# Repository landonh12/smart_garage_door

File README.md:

# Smart Garage Door Controller

This is a PCB made to house a NodeMCU-ESP32S to control my Genie Garage Door. It replaces the wall controller that was installed when we purchased the home.

The original circuit was simple - short RED and WHITE wires to open and close the door, and divide the voltage between RED and WHITE to toggle the garage light.

I used FETs for this - RFP30N06LEs to be exact. The board also supports STD26P3LLH6 FETs.

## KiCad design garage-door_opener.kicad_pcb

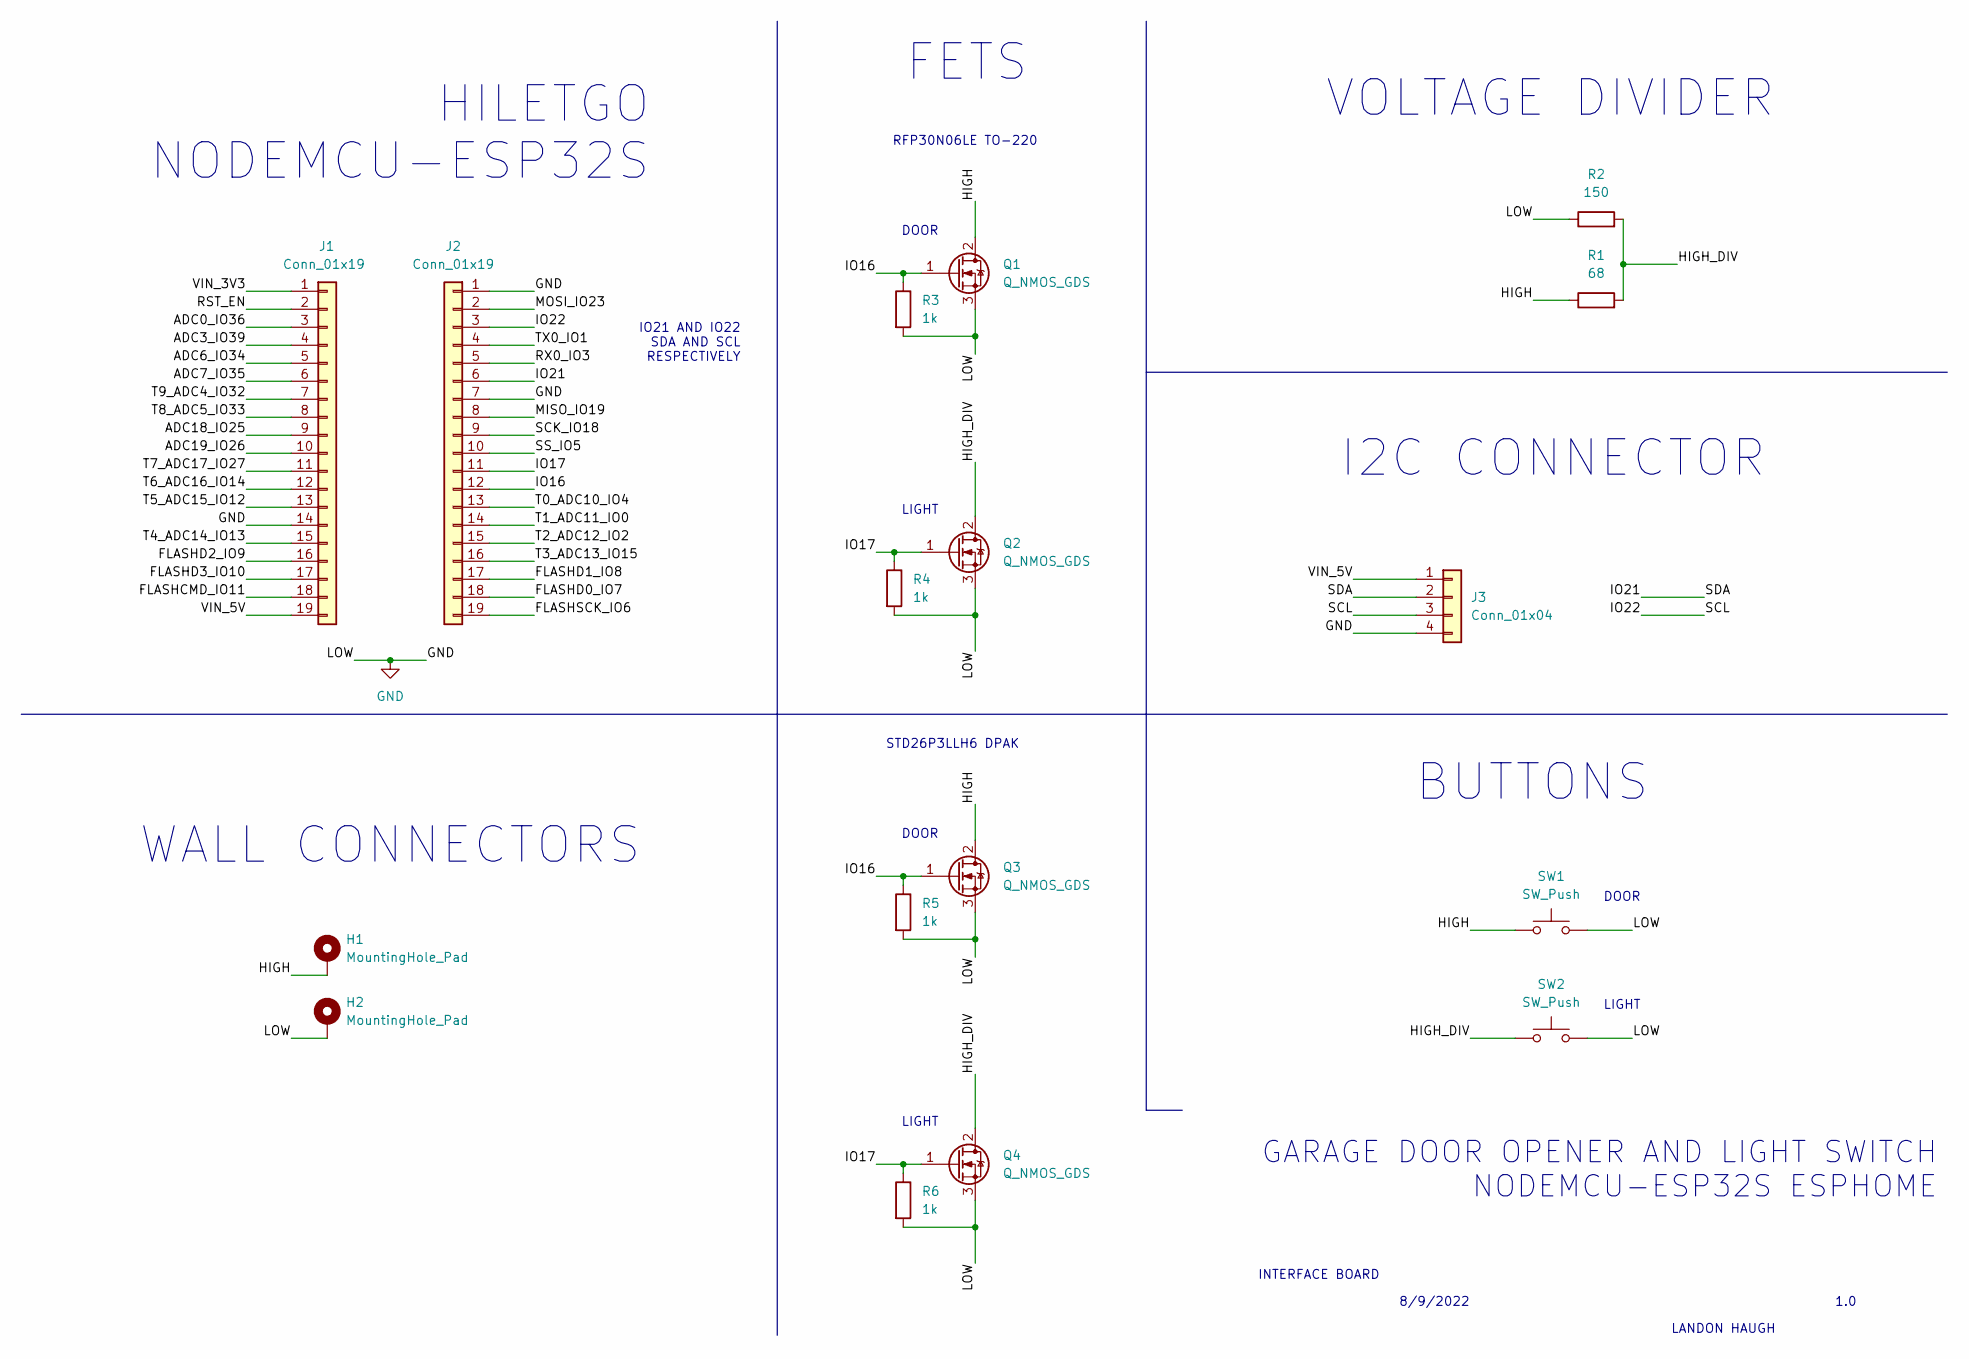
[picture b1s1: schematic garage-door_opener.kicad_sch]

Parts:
H1, H2: MountingHole_Pad; MountingHole_3.2mm_M3_DIN965_Pad_TopBottom
J1, J2: Conn_01x19; PinHeader_1x19_P2.54mm_Vertical
J3: Conn_01x04; PinHeader_1x04_P2.54mm_Vertical
Q1, Q2: Q_NMOS_GDS; TO-220-3_Horizontal_TabDown
Q3, Q4: Q_NMOS_GDS; TO-252-2
R1: 68; R_Axial_DIN0207_L6.3mm_D2.5mm_P10.16mm_Horizontal
R2: 150; R_Axial_DIN0207_L6.3mm_D2.5mm_P10.16mm_Horizontal
R3, R4, R5, R6: 1k; R_Axial_DIN0207_L6.3mm_D2.5mm_P10.16mm_Horizontal
SW1, SW2: SW_Push; SW_PUSH-12mm

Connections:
/ADC0_IO36: J1.3
/ADC3_IO39: J1.4
/ADC6_IO34: J1.5
/ADC7_IO35: J1.6
/ADC18_IO25: J1.9
/ADC19_IO26: J1.10
/FLASHCMD_IO11: J1.18
/FLASHD0_IO7: J2.18
/FLASHD1_IO8: J2.17
/FLASHD2_IO9: J1.16
/FLASHD3_IO10: J1.17
/FLASHSCK_IO6: J2.19
/HIGH: H1.1, Q1.2 (D), Q3.2 (D), R1.1, SW1.1
/HIGH_DIV: Q2.2 (D), Q4.2 (D), R1.2, R2.2, SW2.1
/IO16: J2.12, Q1.1 (G), Q3.1 (G), R3.1, R5.1
/IO17: J2.11, Q2.1 (G), Q4.1 (G), R4.1, R6.1
/IO21: J2.6, J3.2
/IO22: J2.3, J3.3
/MISO_IO19: J2.8
/MOSI_IO23: J2.2
/RST_EN: J1.2
/RX0_IO3: J2.5
/SCK_IO18: J2.9
/SS_IO5: J2.10
/T0_ADC10_IO4: J2.13
/T1_ADC11_IO0: J2.14
/T2_ADC12_IO2: J2.15
/T3_ADC13_IO15: J2.16
/T4_ADC14_IO13: J1.15
/T5_ADC15_IO12: J1.13
/T6_ADC16_IO14: J1.12
/T7_ADC17_IO27: J1.11
/T8_ADC5_IO33: J1.8
/T9_ADC4_IO32: J1.7
/TX0_IO1: J2.4
/VIN_3V3: J1.1
/VIN_5V: J1.19, J3.1
GND: H2.1, J1.14, J2.1, J2.7, J3.4, Q1.3 (S), Q2.3 (S), Q3.3 (S), Q4.3 (S), R2.1, R3.2, R4.2, R5.2, R6.2, SW1.2, SW2.2

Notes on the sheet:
VOLTAGE DIVIDER
WALL CONNECTORS
LANDON HAUGH
DOOR
IO21 AND IO22 SDA AND SCL RESPECTIVELY
HILETGO NODEMCU-ESP32S
LIGHT
INTERFACE BOARD
STD26P3LLH6 DPAK
1.0
RFP30N06LE TO-220
I2C CONNECTOR
GARAGE DOOR OPENER AND LIGHT SWITCH NODEMCU-ESP32S ESPHOME
FETS
BUTTONS
8/9/2022

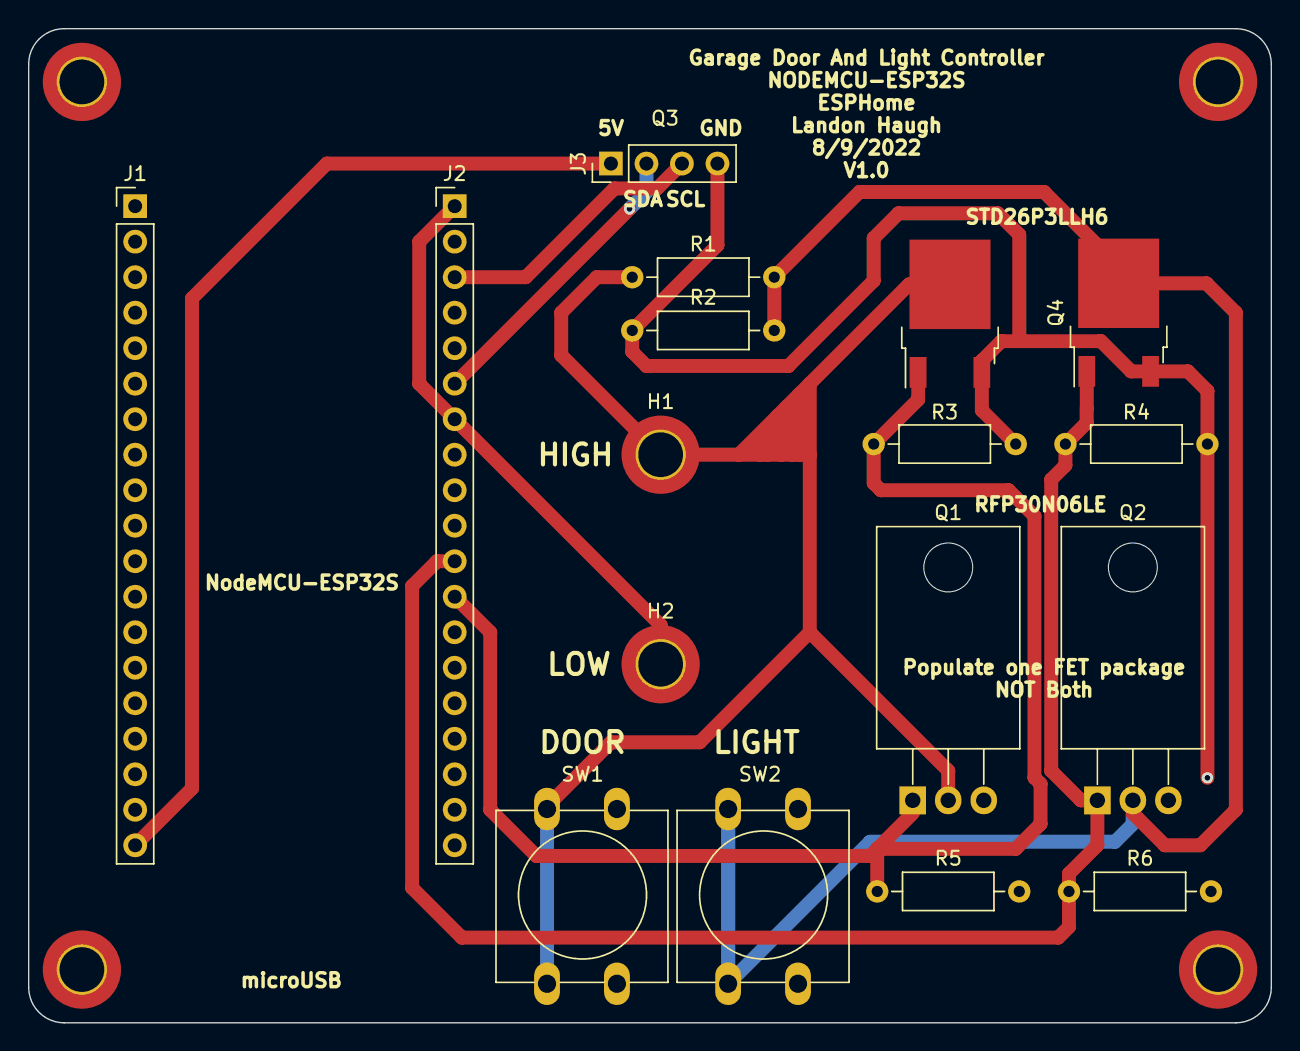
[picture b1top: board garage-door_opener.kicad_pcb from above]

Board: 2 copper layers, 88.9 x 71.1 mm, 19 parts (0 on the bottom side), 8 nets.

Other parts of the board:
mnt: MountingHole_3.2mm_M3_DIN965_Pad_TopBottom
mnt#2: MountingHole_3.2mm_M3_DIN965_Pad_TopBottom

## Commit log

2022-08-10 Add extra details to README.
